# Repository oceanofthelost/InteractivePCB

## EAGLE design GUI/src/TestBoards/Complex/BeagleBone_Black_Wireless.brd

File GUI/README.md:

This project is based on [Interactive BOM](https://github.com/openscopeproject/InteractiveHtmlBom), but being modified to work for eaglecad

Build istruction for Windows:

1) Install [npm for Windows](https://www.guru99.com/download-install-node-js.html#1).  
2) Clone or download this repo. 
2) Navigate to the folder where did you clone it/unpack it. 
3) Hold Shift + Right Click on **GUI** folder and select *Open command window here* or *Open PowerShell window here*.
4) Type **build.bat** and press *Enter*.
5) All done and you have new index.js file :) .

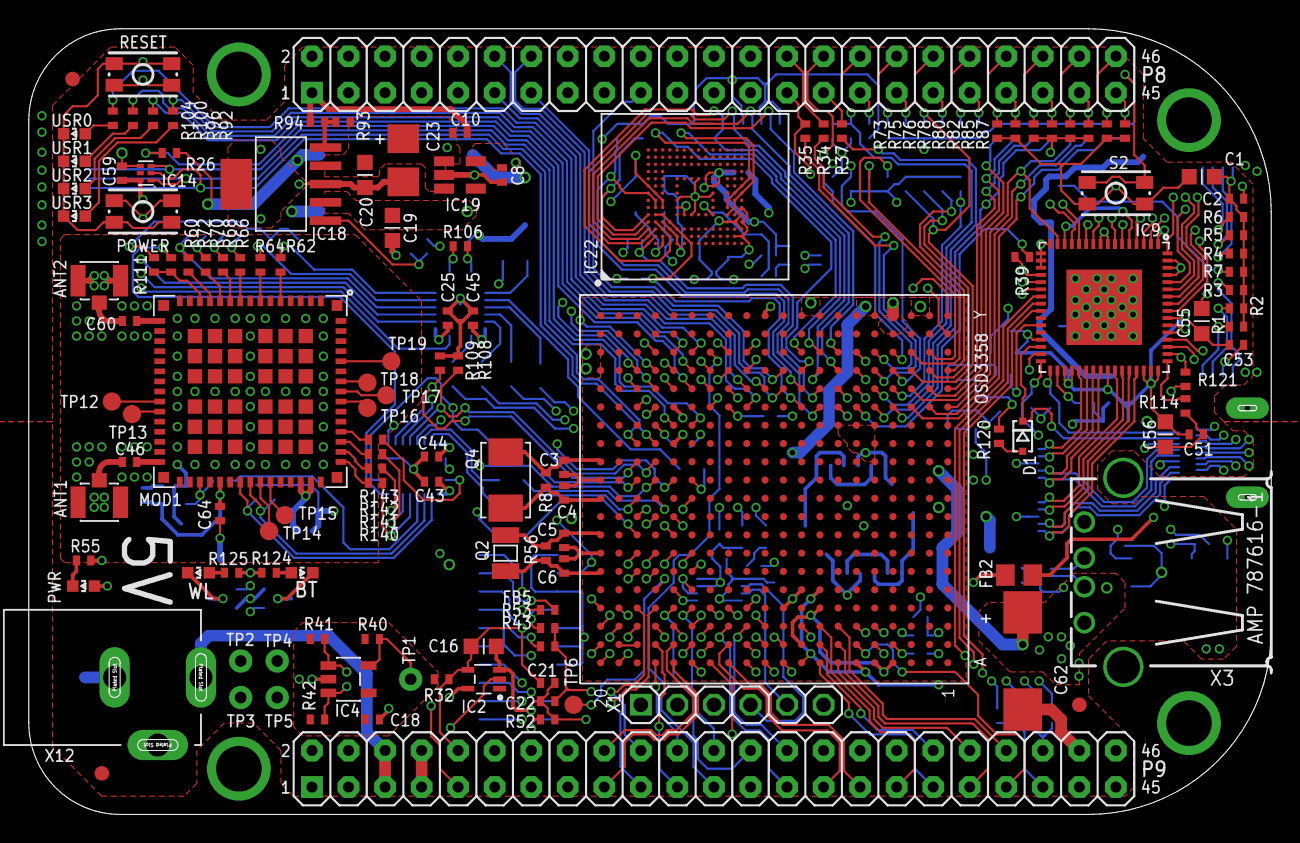
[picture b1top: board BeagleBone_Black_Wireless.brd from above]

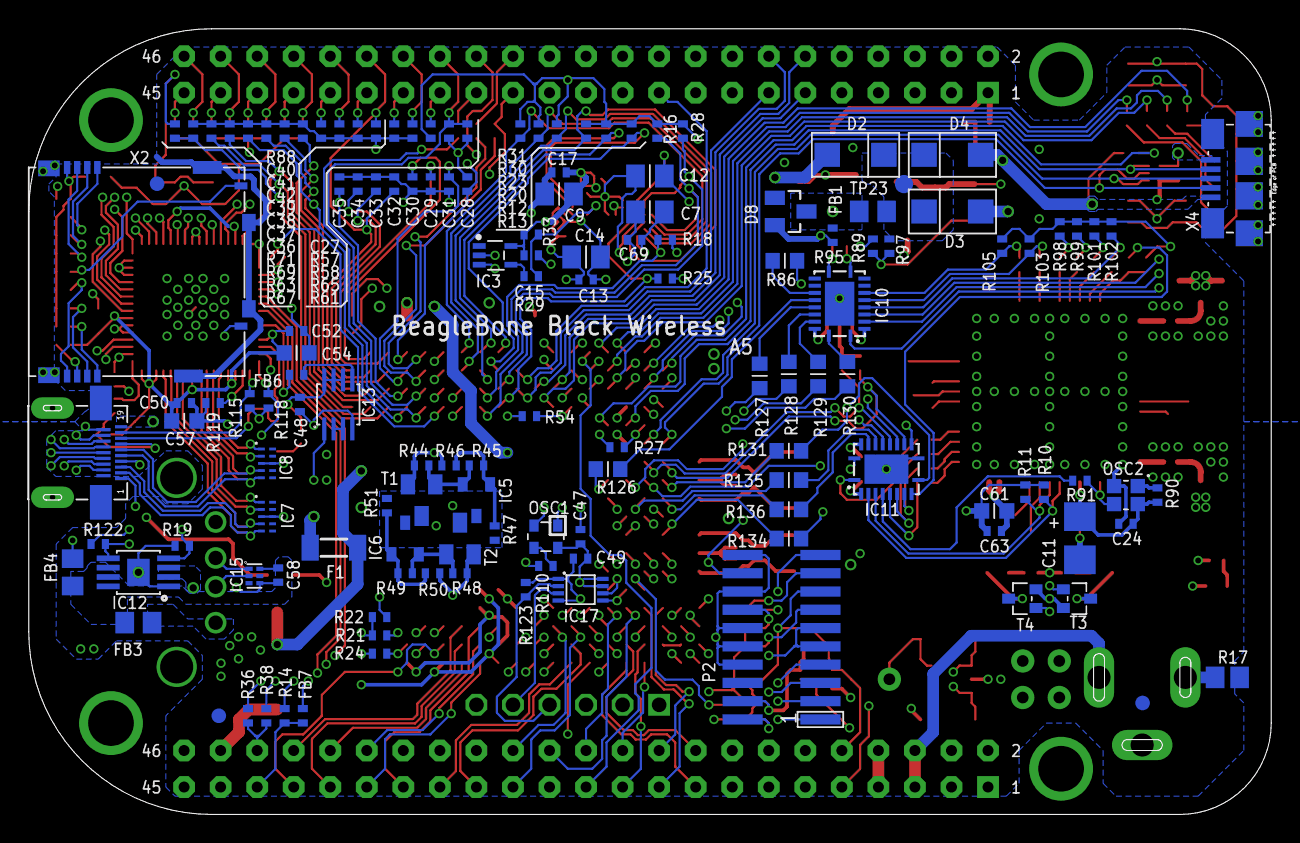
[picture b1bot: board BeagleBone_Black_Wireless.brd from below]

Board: 6 copper layers, 86.4 x 54.6 mm, 275 parts (139 on the bottom side), 262 nets.

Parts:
ANT1, ANT2: U.FL-R-SMT-1(10); U.FL-R-SMT-1
BT: LTST-C191TBKT; 0603-LED
C1: 10uF,10V; C0603K
C2, C13, C15, C17, C18, C21, C22, C24, C25, C43, C44, C45, C47, C48, C49, C50, C51, C52, C53, C58, C59, C63, C69: .1uF, 6.3V; C0402K
C3, C4, C5, C6: 18pF, 50V; C0402K
C7: 4.7uF, 6.3V; C0805K
C8, C10: 1uF; C0402K
C9, C12, C14: 2.2uF, 6.3V; C0805K
C11, C23: 47uF DNP; CT3528
C16, C54, C55, C56, C57: 2.2uF, 6.3V; C0603K
C19, C20, C61: 10uF, 6.3V; C0603K
C27, C28, C29, C30, C31, C32, C33, C34, C35, C36, C37, C38, C39, C40, C41, C42: 47pF, 6.3V; C0402K
C46, C60: 10pF; C0402K
C62: 220uF 6.3V; D/7343-31W
C64: 1uF, 6.3V; C0402K
D1: RB751V40,115; SOD323(NXP)REFLOW
D2: STPS140A DNP; DIODE_SMA
D3, D4: STPS140A; DIODE_SMA
D8: BAT54C; SOT23
F1: 1206L025YR; SM-1206
FB1: 220 Ohm 800mA; 0805-RESISTOR
FB2: 2.5k Ohm (BLM18BD252SN1D); 0805-RESISTOR
FB3: 150 Ohm 800mA; 0805-RESISTOR
FB4: 0.1 Ohm, 0805; 0805-RESISTOR
FB5, FB6, FB7: 1k BLM15AG102SN1D; R0402
FUD1, FUD2, FUD3, FUD4, FUD5, FUD6: FIDUCIAL; FIDUCIAL_40MIL
IC1: OSD3358
IC2: SN74LVC1G07DCK; SC70(TI-DCK)
IC3: SN74LVC1G06DCK; SC70(TI-DCK)
IC4: 24LC32AT-I/OT; SOT23-5(MICROCHIP)
IC5: TLVH431 (SOT-23-3); DBZ_R-PDSO-G3
IC6: DNP TLVH431 (SOT-23-3); DBZ_R-PDSO-G3
IC7, IC8: IP4283CZ10-TBR; SOT1176-1(NXP)
IC9: TDA19988BHN/C1,557; SOT804-4(NXP)
IC10, IC11: TXS0108ERGYR; R-PVQFN-N20(TI)
IC12: TPS2051BDGN; MSOP-POWER.PAD-8(TI)
IC13: SN74AUC1G74; SM8-8(TI)
IC14, IC15: TPD4S012DRY; SON-6(TI)-DRY
IC17: SN74LVC2G241DCUR; VSSOP8(TI)
IC18: TL1963ADCQR; SOT-223(DCQ_R-PDSO-G6_TI)
IC19: AP2112K-1.8TRG1 3.3V; SOT23-5
IC22: MICRON_EMMC_153
MGT1, MGT2, MGT3, MGT4: MOUNTING_HOLE
MOD1: WL1835MODGBMOCT; MOC-100(TI)
OSC1: ASDMB-24.576MHZ-LC-T; OSCILLATOR-2.5X2.0-BBB
OSC2: NZ2520SB-32.768KHZ-NSA3534C; NZ2520S
P2: JTAG
P8, P9: TH-2X23
POWER: MINI_PUSHBUTTON
PWR: LTST-C191TBKT; 0603-LED
Q2: 32.768kHz; CRYSTAL_3.2X1.5
Q4: 24 MHz; CRYSTAL_5X3.2MM
R1, R2, R3, R4, R5, R6, R7, R12, R13, R16, R18, R19, R20, R23, R24, R25, R28, R30, R31, R32, R33, R40, R119, R121: 10k, 1%; R0402
R8: 1M, 1%; R0402
R10, R11: 150k; R0402
R14, R26, R27, R29, R35, R36, R37, R38, R39, R54, R114, R122: 0, 1%; R0402
R17: .1, 0805; R0805
R21, R22, R43, R52, R53, R55: 4.75k, 1%; R0402
R34: 22; R0402
R41, R42, R115, R118: 1.5k, 1%; R0402
R44: 499; R0402
R45, R49: DNP; R0402
R46: 10k 1%; R0402
R47: 40.2k 1%; R0402
R48: DNP 499; R0402
R50: DNP 10k 1%; R0402
R51: DNP 40.2k 1%; R0402
R56: DNP 1M, 1%; R0402
R57, R58, R61, R63, R65, R67, R69, R71, R73, R75, R76, R78, R80, R82, R85, R87, R123: 100k, 1%; R0402
R60, R62, R64, R66, R68, R70, R72, R140, R141, R142, R143: 33, 5%; R0402
R86, R126, R127, R128, R129, R130, R131, R134, R135, R136: 33, 5%; R0603
R88: 100, 1%; R0402
R89, R90, R92, R96, R100, R104, R124, R125: 1k; R0402
R91: 0 DNP; R0402
R93: 7.15k; R0402
R94: 4.12k; R0402
R95: 1M; R0402
R97, R108, R109: DNP 1k; R0402
R98, R99, R101, R102, R103, R105: 10k; R0402
R106: 1.5k; R0402
R110: 33; R0402
R111: DNP 10k; R0402
R120: 27k, 1%; R0402
RESET: MINI_PUSHBUTTON
S2: MINI_PUSHBUTTON
T1: MMBT2907; SOT23-BEC
T2: DNP MMBT2907; SOT23-BEC
T3, T4: BSS138W-7-F; SOT-323(DIODES)
TP1, TP2, TP3, TP4, TP5: TESTPAD/W_HOLE_1X1
TP6, TP12, TP13, TP14, TP15, TP16, TP17, TP18, TP19, TP23: PTR1B1,27; B1,27
USR0, USR1, USR2, USR3: LTST-C191TBKT; 0603-LED
WL: LTST-C191TBKT; 0603-LED
X1: TH-1X6
X2: SCHA5B0200
X3: USB_HOST_HORIZONTAL_W/CHASSIS_GND
X4: 10118192-0001LF; 10118192-0001LF(MICRO-USB-B-AMPHENOL-FCI)
X5: 10118241-001RLF; HDMI-TYPE-D-10118241
X12: PJ-102B_POWER_CON

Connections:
1.8V-WIFI: C8.1, C11.+, C24.1, C25.1, C43.1, C64.1, IC10.2, IC11.2, IC19.5, MOD1.38, OSC2.4, R90.1, R98.1, R99.1, R101.1, R102.1, R103.1, R105.1, R111.1
3.3V-WIFI: C10.1, C20.1, C23.+, C44.1, C45.1, C61.1, C63.1, IC10.19, IC11.19, IC18.4, IC19.1, IC19.3, MOD1.46, MOD1.47, R93.1, R124.2, R125.2
5V_IN: C19.1, D8.3, FB1.2, IC18.2, R95.1
12MHZ: FB6.2, IC9.27
12M_LOOP: IC13.2, IC13.3
32.768KHZ: MOD1.36, OSC2.3, R91.2
AGND: IC1.A6, IC1.A9, IC1.E8, P9.34
AIN0: IC1.B6, P9.39
AIN1: IC1.C7, P9.40
AIN2: IC1.B7, P9.37
AIN3: IC1.A7, P9.38
AIN4: IC1.C8, P9.33
AIN5: IC1.B8, P9.36
AIN6: IC1.A8, P9.35
AIN7: IC1.C9, R21.2, R22.1
ALT.BT.EN: IC11.17, R135.2
ALT.BUFF.OE: IC10.10, IC11.10, R106.1, R131.1
ALT.WL.CLK: IC10.15, R126.2
ALT.WL.CMD: IC10.14, R86.2
ALT.WL.D0: IC10.20, R130.2
ALT.WL.D1: IC10.18, R129.2
ALT.WL.D2: IC10.17, R128.2
ALT.WL.D3: IC10.16, R127.2
ALT.WL.EN: IC11.18, R136.2
ALT.WL.IRQ: IC11.12, R134.2
BAT_TEMP: IC1.W1, TP4.P$1
BAT_VOLT: IC1.Y1, TP3.P$1
BT_EN: IC11.4, MOD1.41, R11.1, T4.G
BT_EN.SIP: IC1.K17, R135.1
BT_HCI_CTS: IC11.8, R141.2
BT_HCI_CTS.SIP: IC1.M17, IC11.15, R108.1
BT_HCI_RTS: IC11.6, R140.2
BT_HCI_RTS.SIP: IC1.M18, IC11.13, R109.1
BT_HCI_RX: IC11.1, R143.2
BT_HCI_RX.SIP: IC1.L17, IC11.14
BT_HCI_TX: IC11.7, R142.2
BT_HCI_TX.SIP: IC1.L16, IC11.20
CEC: D1.C, IC9.30, X5.15
CGND: MGT1.P$1, MGT2.P$1, MGT3.P$1, MGT4.P$1, R17.2, X2.CGND1, X2.CGND2, X2.CGND3, X2.CGND4, X2.CGND5, X2.CGND6, X3.5, X3.6, X4.CGND1, X4.CGND2, X4.CGND3, X4.CGND4, X4.CGND5, X4.CGND6, X5.CG1, X5.CG2, X5.CG3, X5.CG4
CLKOUT2: FB7.1, IC11.16, P2.18, P9.41, R14.1
DVI_5V: F1.1, R115.1, R118.1, X5.19
EHRPWM1A: IC1.U14, P9.14
EHRPWM1B: IC1.T14, P9.16
EHRPWM2A: IC1.U10, P8.19
EHRPWM2B: IC1.T10, P8.13
EMMC_RSTN: IC22.K5, R29.1, R33.1
EXT_SWING: IC9.34, R119.1
GND: ANT1.GND1, ANT1.GND2, ANT2.GND1, ANT2.GND2, C1.2, C2.2, C7.2, C8.2, C9.2, C10.2, C11.-, C12.2, C13.2, C14.2, C15.2, C16.2, C17.2, C18.2, C19.2, C20.2, C21.2, C22.2, C23.-, C24.2, C25.2, C27.2, C28.2, C29.2, C30.2, C31.2, C32.2, C33.2, C34.2, C35.2, C36.2, C37.2, C38.2, C39.2, C40.2, C41.2, C42.2, C43.2, C44.2, C45.2, C47.2, C48.2, C49.2, C50.2, C51.2, C52.2, C53.2, C54.2, C55.2, C56.2, C57.2, C58.2, C59.2, C61.2, C62.-, C63.2, C64.2, C69.2, D8.2, IC1.A1, IC1.A18, IC1.E19, IC1.E20, IC1.F8, IC1.F19, IC1.G8, IC1.G9, IC1.G11, IC1.G12, IC1.G19, IC1.H6, IC1.H7, IC1.H8, IC1.H9, IC1.H10, IC1.H12, IC1.H19, IC1.J6, IC1.J7, IC1.J8, IC1.J9, IC1.J10, IC1.J11, IC1.J19, IC1.J20, IC1.K7, IC1.K9, IC1.K10, IC1.K11, IC1.K19, IC1.L10, IC1.L11, IC1.L12, IC1.L13, IC1.L19, IC1.M6, IC1.M7, IC1.M8, IC1.M9, IC1.M10, IC1.M12, IC1.M14, IC1.M19, IC1.N7, IC1.N10, IC1.N11, IC1.N14, IC1.N19, IC1.N20, IC1.P19, IC1.P20, IC1.R19, IC1.R20, IC1.T19, IC1.T20, IC1.U19, IC1.V1, IC1.V18, IC1.V19, IC1.W2, IC1.W3, IC1.W5, IC1.W6, IC1.W7, IC1.W8, IC1.W9, IC1.W10, IC1.W11, IC1.W12, IC1.W13, IC1.W14, IC1.W15, IC1.W16, IC1.W17, IC1.W18, IC1.W19, IC1.W20, IC1.Y7, IC1.Y10, IC1.Y12, IC1.Y15, IC1.Y18, IC2.3, IC3.3, IC4.2, IC7.3, IC7.8, IC8.3, IC8.8, IC9.8, IC9.9, IC9.16, IC9.17, IC9.18, IC9.19, IC9.53, IC9.54, IC9.61, IC9.62, IC9.63, IC9.65, IC10.11, IC10.TP, IC11.11, IC11.TP, IC12.1, IC12.9, IC13.4, IC14.4, IC15.4, IC17.1, IC17.4, IC18.3, IC18.6, IC19.2, IC22.C4, IC22.E7, IC22.G5, IC22.H10, IC22.K8, IC22.N2, IC22.N5, IC22.P4, IC22.P6, MOD1.1, MOD1.7, MOD1.9, MOD1.15, MOD1.16, MOD1.17, MOD1.19, MOD1.20, MOD1.23, MOD1.24, MOD1.28, MOD1.29, MOD1.30, MOD1.31, MOD1.33, MOD1.34, MOD1.35, MOD1.37, MOD1.39, MOD1.44, MOD1.45, MOD1.48, MOD1.49, MOD1.54, MOD1.55, MOD1.59, MOD1.61, MOD1.63, MOD1.64, MOD1.G1, MOD1.G2, MOD1.G3, MOD1.G4, MOD1.G5, MOD1.G6, MOD1.G7, MOD1.G8, MOD1.G9, MOD1.G10, MOD1.G11, MOD1.G12, MOD1.G13, MOD1.G14, MOD1.G15, MOD1.G16, MOD1.G17, MOD1.G18, MOD1.G19, MOD1.G20, MOD1.G21, MOD1.G22, MOD1.G23, MOD1.G24, MOD1.G25, MOD1.G26, MOD1.G27, MOD1.G28, MOD1.G29, MOD1.G30, MOD1.G31, MOD1.G32, MOD1.G33, MOD1.G34, MOD1.G35, MOD1.G36, OSC1.2, OSC2.2, P2.4, P2.8, P2.10, P2.12, P2.16, P2.20, P8.1, P8.2, P9.1, P9.2, P9.43, P9.44, P9.45, P9.46, POWER.1, POWER.2, R10.2, R11.2, R17.1, R19.2, R22.2, R24.1, R27.2, R52.2, R55.1, R57.1, R61.1, R63.1, R65.1, R67.1, R69.1, R71.1, R73.1, R75.1, R85.1, R87.1, R94.2, R95.2, R106.2, R108.2, R109.2, R114.1, R119.2, R123.2, RESET.1, RESET.2, S2.3, S2.4, T3.S, T4.S, TP5.P$1, USR0.K, USR1.K, USR2.K, USR3.K, X1.1, X2.6, X2.GND, X3.4, X4.GND, X5.4, X5.7, X5.10, X5.13, X5.16, X12.OUT
GPIO0_7: P9.42, R36.1, R38.1
GPIO0_26: IC1.T11, P8.14
GPIO0_27: IC1.U12, P8.17
GPIO1_12: IC1.T12, P8.12
GPIO1_13: IC1.R12, P8.11
GPIO1_14: IC1.V13, P8.16
GPIO1_15: IC1.U13, P8.15
GPIO1_16: P9.15, R54.1
GPIO1_16.SIP: IC1.R13, R54.2
GPIO1_17: IC1.V14, P9.23
GPIO1_28: IC1.U18, P9.12
GPIO1_29: IC1.V6, P8.26
GPIO2_1: IC1.V12, P8.18
GPIO3_19: IC1.C13, P9.27
GPIO3_21: IC1.A14, P9.25, R110.2
HDMI.DSCL: IC9.33, R115.2, X5.17
HDMI.DSDA: IC9.32, R118.2, X5.18
HDMICLK_DIS#: IC1.V17, OSC1.1
HDMI_1V8: C50.1, C51.1, C52.1, C53.1, C54.1, C55.1, C56.1, C57.1, FB2.2, IC9.5, IC9.14, IC9.29, IC9.35, IC9.36, IC9.41, IC9.46, IC9.47, IC9.48, IC9.55
HDMI_INT: IC1.U16, IC9.50, R121.2
HPD: IC9.31, X5.1
I2C0_SCL: IC1.C16, IC1.C20, IC4.1, IC9.52, R41.2
I2C0_SDA: IC1.C17, IC1.C19, IC4.3, IC9.51, R42.2
I2C1_SCL: IC1.A16, P9.17
I2C1_SDA: IC1.B16, P9.18
I2C2_SCL: IC1.D17, P9.19
I2C2_SDA: IC1.D18, P9.20
JTAG_EMU0: IC1.C14, P2.13, R43.2
JTAG_EMU1: IC1.B14, P2.14, R53.2
JTAG_TCK: IC1.A12, P2.9, P2.11
JTAG_TDI: IC1.B11, P2.3
JTAG_TDO: IC1.A11, P2.7
JTAG_TMS: IC1.C11, P2.1
JTAG_TRSTN: IC1.B10, P2.2, R52.1
LCD.CLOCK: IC9.4, P8.28, R34.1
LCD.D0.B0--B3: C42.1, IC1.R1, IC9.15, P8.45, R87.2
LCD.D1.B1--B4: C41.1, IC1.R2, IC9.13, P8.46, R85.2
LCD.D2.B2--B5: C40.1, IC1.R3, IC9.12, P8.43, R82.1, R88.1
LCD.D3.B3--B6: C39.1, IC1.R4, IC9.11, P8.44, R80.1
LCD.D4.B4--B7: C38.1, IC1.T1, IC9.10, P8.41, R78.1
LCD.D5.G0--G2: C37.1, IC1.T2, IC9.7, P8.42, R76.1
LCD.D6.G1--G3: C36.1, IC1.T3, IC9.6, P8.39, R75.2
LCD.D7.G2--G4: C35.1, IC1.T4, IC9.3, P8.40, R73.2
LCD.D8.G3--G5: C34.1, IC1.U1, IC9.2, P8.37, R71.2
LCD.D9.G4--G6: C33.1, IC1.U2, IC9.1, P8.38, R69.2
LCD.D10.G5--G7: C32.1, IC1.U3, IC9.64, P8.36, R67.2
LCD.D11.R0--R3: C31.1, IC1.U4, IC9.60, P8.34, R65.2
LCD.D12.R1--R4: C30.1, IC1.V2, IC9.59, P8.35, R63.2
LCD.D13.R2--R5: C29.1, IC1.V3, IC9.58, P8.33, R61.2
LCD.D14.R3--R6: C28.1, IC1.V4, IC9.57, P8.31, R58.1
LCD.D15.R4--R7: C27.1, IC1.T5, IC9.56, P8.32, R57.2
LCD.ENABLE: IC9.20, P8.30, R39.1
LCD.HSYNC: IC9.22, P8.29, R37.1
LCD.VSYNC: IC9.21, P8.27, R35.1
LDO_PGOOD: IC1.B5, IC1.B20
LS_BUF_OE: IC1.L18, R131.2
MCU.LCD.CLK: IC1.V5, R34.2
MCU.LCD.EN: IC1.R6, R39.2
MCU.LCD.HS: IC1.R5, R37.2
MCU.LCD.VS: IC1.U5, R35.2
MMC1_CLK: IC1.U9, IC22.M6, P8.21, R31.1
MMC1_CMD: IC1.V9, IC22.M5, P8.20, R30.1
MMC1_DAT0: IC1.U7, IC22.A3, P8.25, R12.1
MMC1_DAT1: IC1.V7, IC22.A4, P8.24, R13.1
MMC1_DAT2: IC1.R8, IC22.A5, P8.5, R16.1
MMC1_DAT3: IC1.T8, IC22.B2, P8.6, R18.1
MMC1_DAT4: IC1.U8, IC22.B3, P8.23, R20.1
MMC1_DAT5: IC1.V8, IC22.B4, P8.22, R23.1
MMC1_DAT6: IC1.R9, IC22.B5, P8.3, R25.1
MMC1_DAT7: IC1.T9, IC22.B6, P8.4, R28.1
unnamed: OSC2.1, R90.2
unnamed: R88.2, S2.1, S2.2
unnamed: FB5.1, IC1.A15
unnamed: PWR.K, R55.2
unnamed: IC18.1, R89.2, R97.2
unnamed: C4.1, IC1.K20, Q4.1, R8.1
unnamed: C3.1, IC1.M20, Q4.2, R8.2
unnamed: IC1.C6, IC1.D19
unnamed: IC18.5, R93.2, R94.1
unnamed: C3.2, C4.2, IC1.L20
unnamed: C5.2, C6.2, IC1.G20
unnamed: ANT2.SIG, C60.1
unnamed: ANT1.SIG, C46.1
unnamed: C46.2, MOD1.32
unnamed: R100.1, USR1.A
unnamed: R96.1, USR2.A
unnamed: R92.1, USR3.A
unnamed: C60.2, MOD1.18
unnamed: IC1.P17, R27.1
unnamed: IC1.B4, R24.2
unnamed: T3.D, WL.K
unnamed: IC1.D13, R14.2
unnamed: FB7.2, IC1.D14
unnamed: IC1.R14, IC3.2
unnamed: IC3.4, R29.2
unnamed: MOD1.26, TP12.TP
unnamed: R104.1, USR0.A
unnamed: MOD1.27, TP13.TP
unnamed: C5.1, IC1.H20, Q2.P$1, R56.2
unnamed: C6.1, IC1.F20, Q2.P$2, R56.1
unnamed: MOD1.42, TP14.TP
unnamed: MOD1.43, TP15.TP
unnamed: MOD1.56, TP16.TP
unnamed: MOD1.57, TP17.TP
unnamed: OSC1.3, R110.1
unnamed: MOD1.58, TP18.TP
unnamed: MOD1.60, TP19.TP
unnamed: IC1.P15, R26.1
unnamed: C7.1, C69.1, IC22.C2
unnamed: IC1.C18, R36.2
unnamed: IC1.B12, R38.2
unnamed: IC5.2, R44.2, R45.1, T1.B
unnamed: IC5.1, R45.2, R46.2, R47.1
unnamed: IC6.2, R48.2, R49.1, T2.B
unnamed: IC6.1, R49.2, R50.2, R51.1
unnamed: IC4.5, R40.2, TP1.P$1
unnamed: BT.K, T4.D
unnamed: R125.1, WL.A
unnamed: FB6.1, IC13.5
unnamed: BT.A, R124.1
unnamed: MOD1.14, R60.1, R111.2
unnamed: MOD1.13, R72.1
unnamed: MOD1.12, R70.1
unnamed: MOD1.11, R68.1
unnamed: D1.A, R120.2
unnamed: MOD1.10, R66.1
unnamed: MOD1.8, R64.1
unnamed: MOD1.6, R62.1
unnamed: MOD1.50, R140.1
unnamed: MOD1.51, R141.1
unnamed: MOD1.52, R142.1
unnamed: MOD1.53, R143.1
PMIC_INT: IC1.B18, IC1.B19
PMIC_NWAKEUP: IC1.A19, IC1.C5
PMIC_PGOOD: IC1.A20, IC1.B15, IC2.2
PWR_BUT: IC1.D20, P9.9, POWER.3, POWER.4
RX<-TX: IC17.3, X1.5
SD.CD: IC1.C15, P2.19, R7.1, X2.CD
SD.CLK: IC1.G17, R3.1, X2.5
SD.CMD: IC1.G18, R4.1, X2.3
SD.D0: IC1.G16, R2.1, X2.7
SD.D1: IC1.G15, R1.1, X2.8
SD.D2: IC1.F18, R6.1, X2.1
SD.D3: IC1.F17, R5.1, X2.2
SELECT_5V: D2.K, D3.K, D4.K, FB1.1, R97.1, TP23.TP
SLOW_CLK: IC11.5, R91.1
SPI1_CS0: IC1.C12, IC9.25, P9.28
SPI1_D0: IC1.B13, IC9.24, P9.29
SPI1_D1: IC1.D12, P9.30
SPI1_SCLK: IC1.A13, IC9.23, P9.31
SYS_5V: C62.+, D2.A, F1.2, IC1.W4, IC1.Y4, IC12.2, IC12.3, P9.7, P9.8
SYS_RESET#: C16.1, C21.1, IC1.A10, IC2.4, P2.15, P9.10, R32.2, RESET.3, RESET.4
TEST: IC9.49, R114.2
TIMER4: IC1.R7, P8.7
TIMER5: IC1.T6, P8.9
TIMER6: IC1.U6, P8.10
TIMER7: IC1.T7, P8.8
TX0+: IC8.5, IC9.40, X5.9
TX0-: IC8.4, IC9.39, X5.11
TX1+: IC7.2, IC9.43, X5.6
TX1-: IC7.1, IC9.42, X5.8
TX2+: IC7.5, IC9.45, X5.3
TX2-: IC7.4, IC9.44, X5.5
TX->RX: IC17.2, R123.1, X1.4
TXC+: IC8.2, IC9.38, X5.12
TXC-: IC8.1, IC9.37, X5.14
UART0_RST#: IC1.E17, TP6.TP
UART0_RXD: IC1.E15, IC17.6
UART0_TXD: IC1.E16, IC17.5
UART1_RXD: IC1.D16, P9.26
UART1_TXD: IC1.D15, P9.24
UART2_RXD: IC1.A17, P9.22
UART2_TXD: IC1.B17, P9.21
UART4_RXD: IC1.T17, P9.11
UART4_TXD: IC1.U17, P9.13
USB1_DRVVBUS: IC1.F15, IC12.4, R19.1
USB1_OC#: IC1.T16, IC12.5, R122.2
USB1_VBUS: FB4.2, IC1.T18
USB.CLIENT.D+: IC1.N17, IC14.1, X4.D+
USB.CLIENT.D-: IC1.N18, IC14.2, X4.D-
USB.CLIENT.ID: IC1.P16, IC14.3, X4.ID
USB.HOST.D+: IC1.R17, IC15.1, X3.3
USB.HOST.D-: IC1.R18, IC15.2, X3.2
USB_DC: C59.1, D4.A, IC1.Y8, IC1.Y9, IC14.6, R26.2, X4.VBUS
USR0: IC1.V15, R104.2
USR1: IC1.U15, R100.2
USR2: IC1.T15, R96.2
USR3: IC1.V16, R92.2
VBUS.HOST: FB3.2, X3.1
VBUS.OUT: C58.1, FB3.1, FB4.1, IC12.6, IC12.7, IC12.8, IC15.6
VDD_1V8: FB2.1, IC1.D10, IC1.E9, IC1.N16, IC1.R16, IC2.5, IC5.3, IC6.3, R47.2, R51.2, T1.C, T2.C
VDD_3V3A: IC1.N5, IC1.P5, IC1.P6, IC1.P7, R44.1, R46.1, T1.E
VDD_3V3AUX: IC1.Y11, PWR.A
VDD_3V3B: C1.1, C2.1, C9.1, C12.1, C13.1, C14.1, C15.1, C17.1, C18.1, C22.1, C47.1, C48.1, C49.1, IC1.U20, IC1.V20, IC3.5, IC4.4, IC13.6, IC13.7, IC13.8, IC17.7, IC17.8, IC22.C6, IC22.E6, IC22.F5, IC22.J10, IC22.K9, IC22.M4, IC22.N4, IC22.P3, IC22.P5, OSC1.4, P2.5, P9.3, P9.4, R1.2, R2.2, R3.2, R4.2, R5.2, R6.2, R7.2, R12.2, R13.2, R16.2, R18.2, R20.2, R21.1, R23.2, R25.2, R28.2, R30.2, R31.2, R32.1, R33.2, R40.1, R41.1, R42.1, R43.1, R48.1, R50.1, R53.1, R58.2, R76.2, R78.2, R80.2, R82.2, R89.1, R120.1, R121.1, R122.1, T2.E, X2.4
VDD_5V: D3.A, IC1.Y5, IC1.Y6, P9.5, P9.6, X12.IN
VDD_ADC: IC1.A4, IC1.A5, IC1.B9, IC1.D8, P9.32
VIN_BAT: IC1.Y2, IC1.Y3, TP2.P$1
WL_EN: IC11.3, MOD1.40, R10.1, T3.G
WL_EN.SIP: IC1.K18, R136.1
WL_IRQ: IC11.9, R60.2
WL_IRQ.SIP: IC1.H18, R134.1
WL_SDIO_CLK: IC10.6, R64.2, R103.2
WL_SDIO_CLK.SIP: IC1.L15, R126.1
WL_SDIO_CMD: IC10.7, R62.2, R105.2
WL_SDIO_CMD.SIP: IC1.J16, R86.1
WL_SDIO_D0: IC10.1, R66.2, R98.2
WL_SDIO_D0.SIP: IC1.J17, R130.1
WL_SDIO_D1: IC10.3, R68.2, R99.2
WL_SDIO_D1.SIP: IC1.J18, R129.1
WL_SDIO_D2: IC10.4, R70.2, R101.2
WL_SDIO_D2.SIP: IC1.K15, R128.1
WL_SDIO_D3: IC10.5, R72.2, R102.2
WL_SDIO_D3.SIP: IC1.H16, R127.1
XDMA_EVENT_INTRO: FB5.2, IC13.1, P2.17

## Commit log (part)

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2018-09-20 Added README
2018-09-20 Move debugging out of index.js
    I assume this is a debugging thing anyway.
    If it's not, and is supposed to be part of it,
    feel free to move it back.
2018-09-20 Split index.js into individual files
2018-09-21 Ported all but 2 functions from html to javascript
2018-09-22 Moved htlm/js listiners to there own JS module
2018-09-24 Removed Qty from displayed BOM
2018-09-24 added top/bottom silkscreen & dimension support.
    The silkscreen for bith the top and bottom is mostly working. Assumption
    is that they are all line segment and not polygons. The pcb outline
    is also supported.
2018-09-25 Removed eslint as project dependancy
2018-09-26 Created release V1.0
2018-09-26 Added TODO to root folder
2018-09-26 Updated filter to highlight active filets
2018-09-26 Updated eagle ulp to generate one entry for each unique value
2018-09-27 Finished adding support for combined values
2018-09-27 Added changelog
2018-09-27 Started tracking package-lock file
2018-09-27 Removed duplicate package-lock file
2018-09-27 Removed refrence lookup
2018-09-27 Updated filter to search reference field
2018-09-27 Updated changelog
2018-09-27 Other half of Eagle ULP for outputting attributes
2018-09-27 Updated BOM element filtering
    Added support for filtering both combined and uncombined BOM entries.
2018-09-27 Updated BOM filtering to look at the attribute value and not name.
    BOM filtering looks at the attribute value instead of just matching
    the name. There is an assumption that if the value is "" (an empty string),
    then don't filter out the part, if the value is set to ANY value, then
    it assumed that the part should be filtered.
2018-09-27 Removed console.log
2018-09-27 Added example output for EagleCAD
2018-09-27 Updated user entries
    User entries are comma separated. Whitespace at the front or back of
    user entries is removed. This way only internal whitespace is used
    when comparing and all other is thrown away.
2018-09-28 Release V1.4
2018-09-28 Converted BUG0001 documents to markdown syntax
2018-09-28 shortened commit hash in markdown file
2018-09-28 Reverted back to my original format
2018-09-28 Have non combined values working
2018-09-28 Working application with new backend
    Finished converting to the new backend. The parts are now read in and
    converted to an internal representation. This representation is then used
    for all application work.
    This commit marks a working application but there is still work needed
    to clean up and simplify the code.
2018-09-28 Changed the sort function to compare by string not by char
2018-09-29 Updated filter to support attributes
2018-09-29 Updated eagle ulp
    Created a function for each section of the json file. Also removed
    generating the bom for front, back, and both. Script generates bom
    data for only both option.
2018-10-07 Half working click parts selection
    clicking a part in the bounding box on the front of the board will
    select the part and highlight its BOM entry and its bounding box.
2018-10-07 The file should never of been tracked
2018-10-07 Release V1.6
2019-03-17 Add python utility to add "Customer Ref" data to json output.
    The "Customer Ref" field in BOM-EX is used to store internal part numbers.
2019-03-19 Updated buglist summary file
2019-03-19 Fixed BUG0004
2019-03-19 Switched commit hash for Github URL
2019-03-21 Started work on adding alternate color for placed part
    A feature was requested to have alternate color for placed parts. This
    is the first commit that
    acts as a proof of concept that the feature could work. This
    implementation works but requires
    a global variable be used right now.
2019-03-21 Removed double click from checkboxes
2019-03-23 Added button to clear filter bar
    A simple HTML/CSS/JS button was created and added to clear the Filter
    bar. An input field of type search was tried but the (x) would not
    appear so I went with adding the button manually.
2019-03-24 Changed storage string for checkboxes to be lowercase
2019-07-14 Update README
    Add build instruction for Windows & change word KiCAD to Eagle.
2019-10-30 Bump cached-path-relative from 1.0.1 to 1.0.2 in /GUI
    Bumps [cached-path-relative](https://github.com/ashaffer/cached-path-relative) from 1.0.1 to 1.0.2.
    - [Release notes](https://github.com/ashaffer/cached-path-relative/releases)
    - [Commits](https://github.com/ashaffer/cached-path-relative/commits)
2019-12-06 Documentation
2019-12-07 Created ULP for generating circle dimension data
2019-12-07 Created Simple EagleCAD PCBs
    Three PCBs were created. Each contains only a PCB shape.
    1) Square
    2) Circle
    3) Lines with arcs
    Each simple board will be used to test the display of simple board
    shapes within the python program and also test that the EagleCAD ULP
2019-12-07 Created board that contains all three shape types
2019-12-07 Fixed bugs in dimension ULP
    1) Width now exports as a float instead of a string. Numbers should be
    exported as numbers and not as a string to stay consistent with rest
    of interchange file data.
    2) Export arcs center point y coordinate as yc, was mistakingly
    set to xc.
2019-12-09 Re factored printing data to file
    All code that was duplicated for printing a line, arc, or a circle to
    a file are now put into a single function which is called when it needs
    to be.
2019-12-09 Finished adding top silkscreen support
    All top silkscreen can now be exported from EagleCAD to the intermediate
    file.
    Implementation of exporting silkscreen for packages comes from
    silk.ulp. This ULP provides most of the framework for working with
    silkscreen on a layer, but it does not take into account text unless
    it is text within a package. To fix this I used the the text exporting
2019-12-11 Updated ULP and Python program to render circle pads
    Since pads are really square and they become round only when the
    roundness parameter is used, I have hard coded a way to display square
    and round pads. If the roundness parameter is zero, then the pad is
    displayed as a polygon while if it is 100%, the the pad is displayed as
    a circle.
    No other pad shapes can currently be displayed. Need to come up with a
2019-12-11 Added 2 new test boards.
    These boards are used to est the different stages of rendering. The BBBW
    comes from an example within EagleCAD. This design is very complex and
    is being used to test all stages of rendering.
    The other brd file was used early on to test that simple silkscreen and
    pads could be displayed.
2019-12-12 Started extracting PCB rending to its own class
    PCB rendering has been put into its own subclass of float canvas. By
    having the PCB rendering as a canvas, it can be directly integrated into
    the wx GUI.
2019-12-12 Removed iBOM_Canvas.py
    iBOM_Canvas is now split into 3 files
    1) PCBCanvas.py
    2) BOM_Tool.py
    3) gui.py
    PCBCanvas takes care of the rendering, BOM_Tool.py is an auto from wxFormBuilder, and gui.py is the
    main entry point for the GUI.
2019-12-12 Added grid item as left hand element.
    Started testing using a grid item for use with the BOM. It looks like I can use the grid as a base
    and the deriving class can represent the bill of material.
2020-04-04 Bump acorn from 5.7.3 to 5.7.4 in /GUI
    Bumps [acorn](https://github.com/acornjs/acorn) from 5.7.3 to 5.7.4.
    - [Release notes](https://github.com/acornjs/acorn/releases)
    - [Commits](https://github.com/acornjs/acorn/compare/5.7.3...5.7.4)
2020-08-11 Resolve GitHub Issue #27:Automatically hide parts
    Fixes issue when if option "Hide Placed Parts" is activated and then
    checking the box for placed part will now hide the part.
2020-08-11 Added debug option
    Currently debug shows only the bounding boxes for all parts. This was
    added to help troubleshoot GitHub Issue #28.
2020-08-13 Updated Arduino example pcbdata.json file
    File is now up to date with the most recent version of eagle ULP.
2020-08-13 Updated simple board to have curved edges
2020-10-14 Update PCB_DataFormat.md
    Removed requirement for having a bounding box set for BOARD. Board should only contain the paths required to draw the board outline(s).
2020-10-15 Moved bug tracking to GitHub
2020-10-15 Updated data interchange format spec
    Expanded on PCB outline to include bounding box for the PCB.
2020-10-15 Updated data interchange specification
    Changed <HEADER> to <METADATA> as this is a more descriptive term for
    this section.
2020-10-16 Example Split.js code for new layouts
    The three example files each contain one of the splits tat the system
    can be in. These were tested uses JSFiddle.
    The key is to not over constrain Split.js as this will cause the split
    to fail. It is also important to use the class type split-horizontal
    and also set the direction in order to get the splits to behave as they
    should.
2020-10-16 Updated ULP to more closely match data format specification.
2020-10-25 Updated example board to be more complex
2020-10-25 Rectangles are now rotated correctly.
2020-10-25 Added rule to ignore EagleCAD backup files
2020-12-16 Adjusted PCB rotation to be consistent with ECAD viewer
2020-12-16 Fixed default rotation angle for initial startup
    Had made change to rotation angle to be between 0-360 in commit
    87fedfeb64e65766b2073c43e4edea73931f60f5. This commit now fixes the
    issue of PCB rotation when the program starts fresh.
2020-12-16 Added support for displaying BOM entries.
    Currently highlighting, sorting, and searching works.
2020-12-18 Started work on adding layer visibility
    THis adds the header row to the layer visibility part of UI.
2020-12-19 Added support for rendering all three via types
2020-12-20 Updated Eagle ULP to output all silkscreen related layers
2020-12-30 Added layer name and visibility selection
2020-12-31 Removed reference to KiCAD
2020-12-31 Created new PCB in EagleCAD that utilizes most export features
2020-12-31 Updated part hit test to use new data format
2020-12-31 Updated rendering of part pads
    All rendering for pads is now done though a single low level interface,
    render_lowlevel. render_pads simply formats the data into a format that
    the lower level drawing functions understands.
2020-12-31 Update to rendering traces
    Trace rendering now uses the low level rendering interface.
2020-12-31 Moved mouse handlers to there own file
    Event handlers for mouse events were all located within the rendering
    file. All mouse event handlers have now moved there own file so the
    rending file only contains rendering related functions.
2020-12-31 Updated sample board
2021-01-01 Fixed bug with via rendering
    When a via is a polygon shape, the size of the via was being rendered
    smaller if a polygon. This was due to the the assumption that the
    polygon was inscribed with a circle, where really the polygon
    circumscribes the circle.
    This commit now calculates the radius that would make the polygon
    inscribed. The radius is then used with the original formula in order
2021-01-01 Removed silk layer from html
    Silkscreen and is now drawn directly to the main layer, so no
    silkscreen layer needs to be supplied.
2021-01-01 Moved pin color settings from CSS to javascript
    To facilitate having colorMaps, color codes are being moved from CSS to
    being configured in Javascript.
    Color settings will now be located in colorMap.js and any request for
    a rending color should go through colorMap.js.
2021-01-01 Added support for light and dark palettes in colormap
    All colors in colormap.js now use an array approach that allows
    for a light or dark color to be set.
2021-01-01 Removed pcbfont.js as it was not used
